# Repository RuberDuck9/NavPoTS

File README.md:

# NavPoTS
The integrated navigation, power, and telemtry system.

(placeholder name btw)

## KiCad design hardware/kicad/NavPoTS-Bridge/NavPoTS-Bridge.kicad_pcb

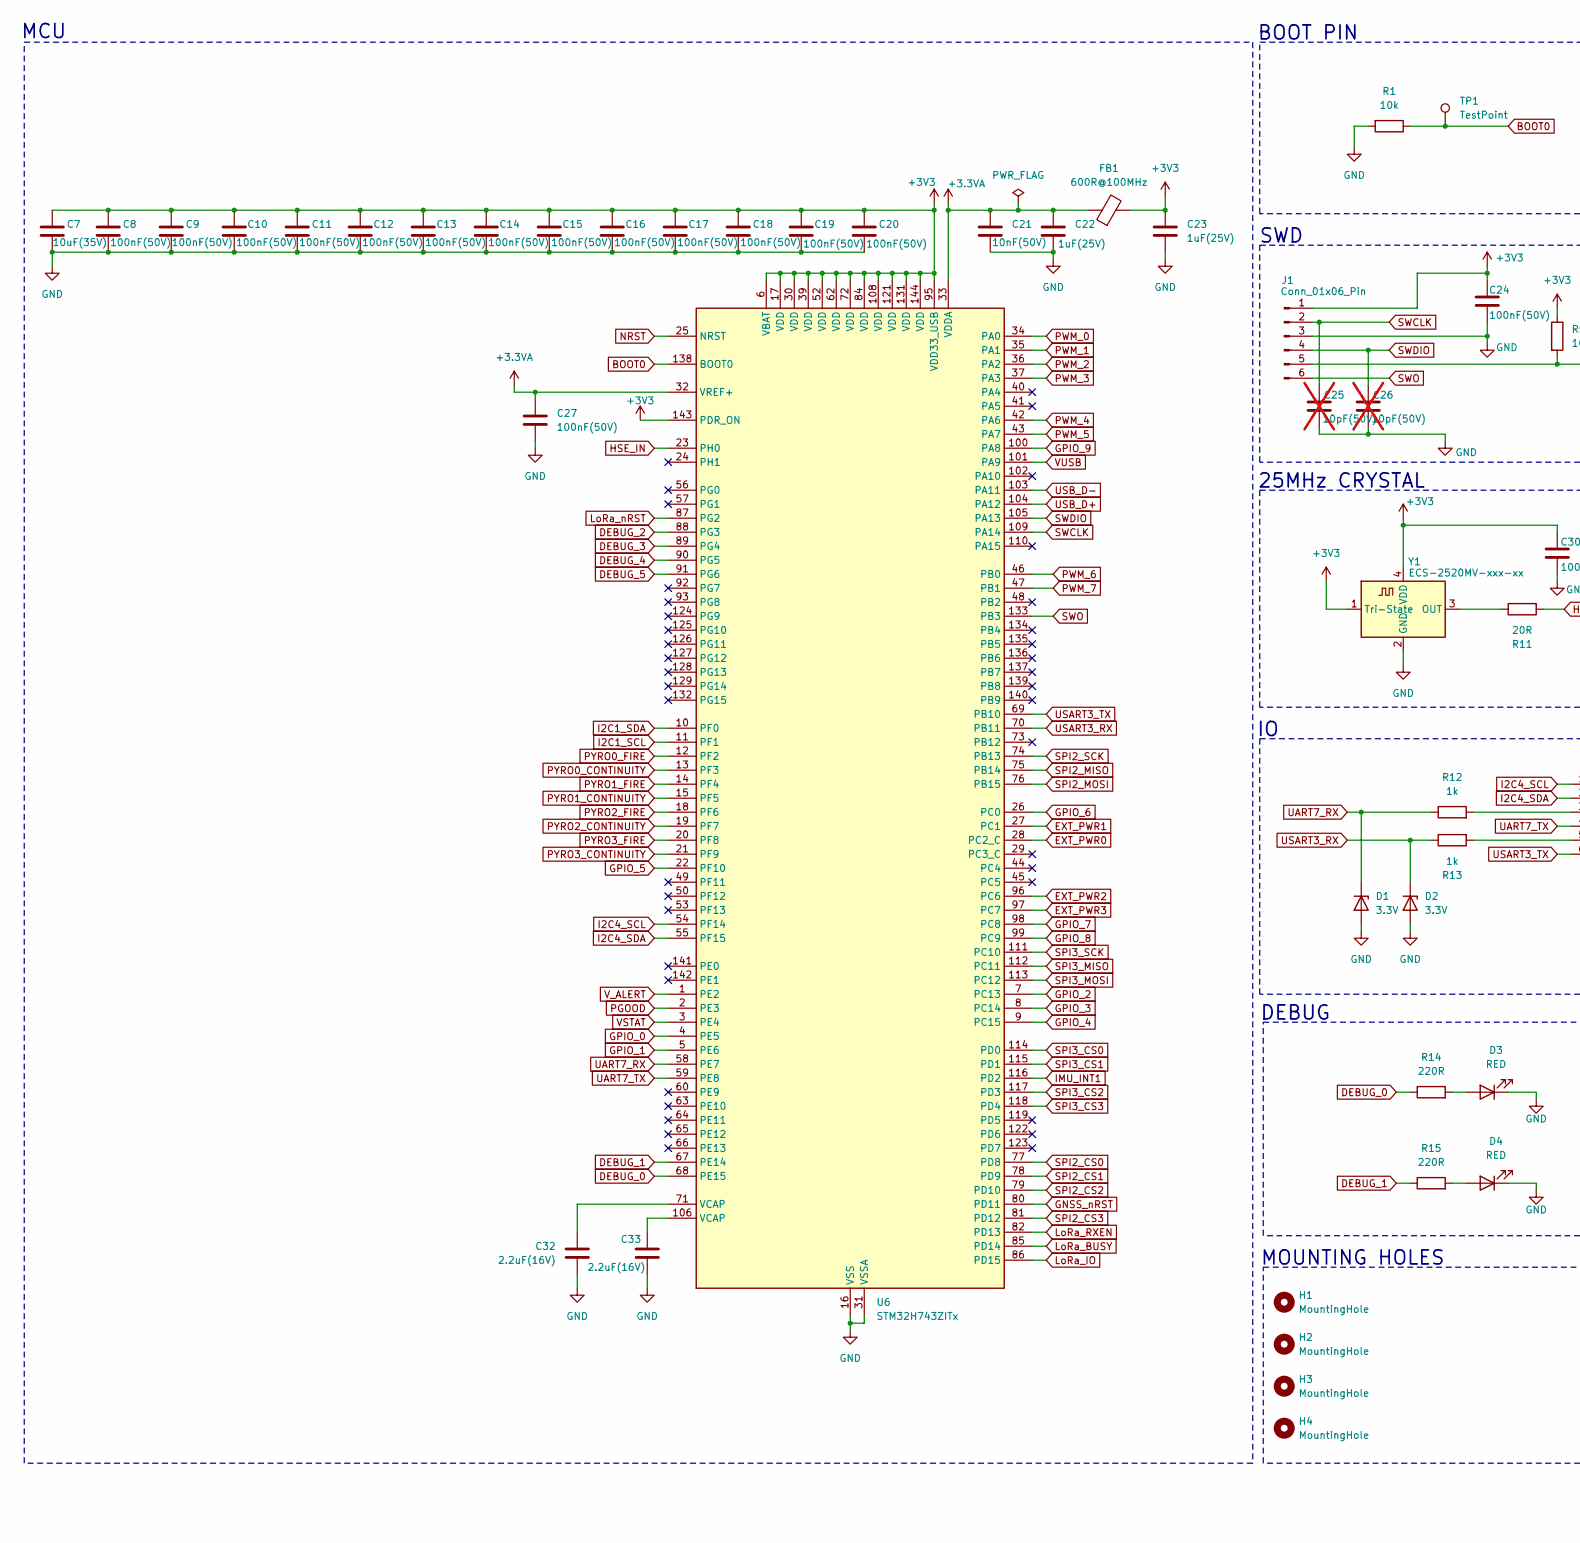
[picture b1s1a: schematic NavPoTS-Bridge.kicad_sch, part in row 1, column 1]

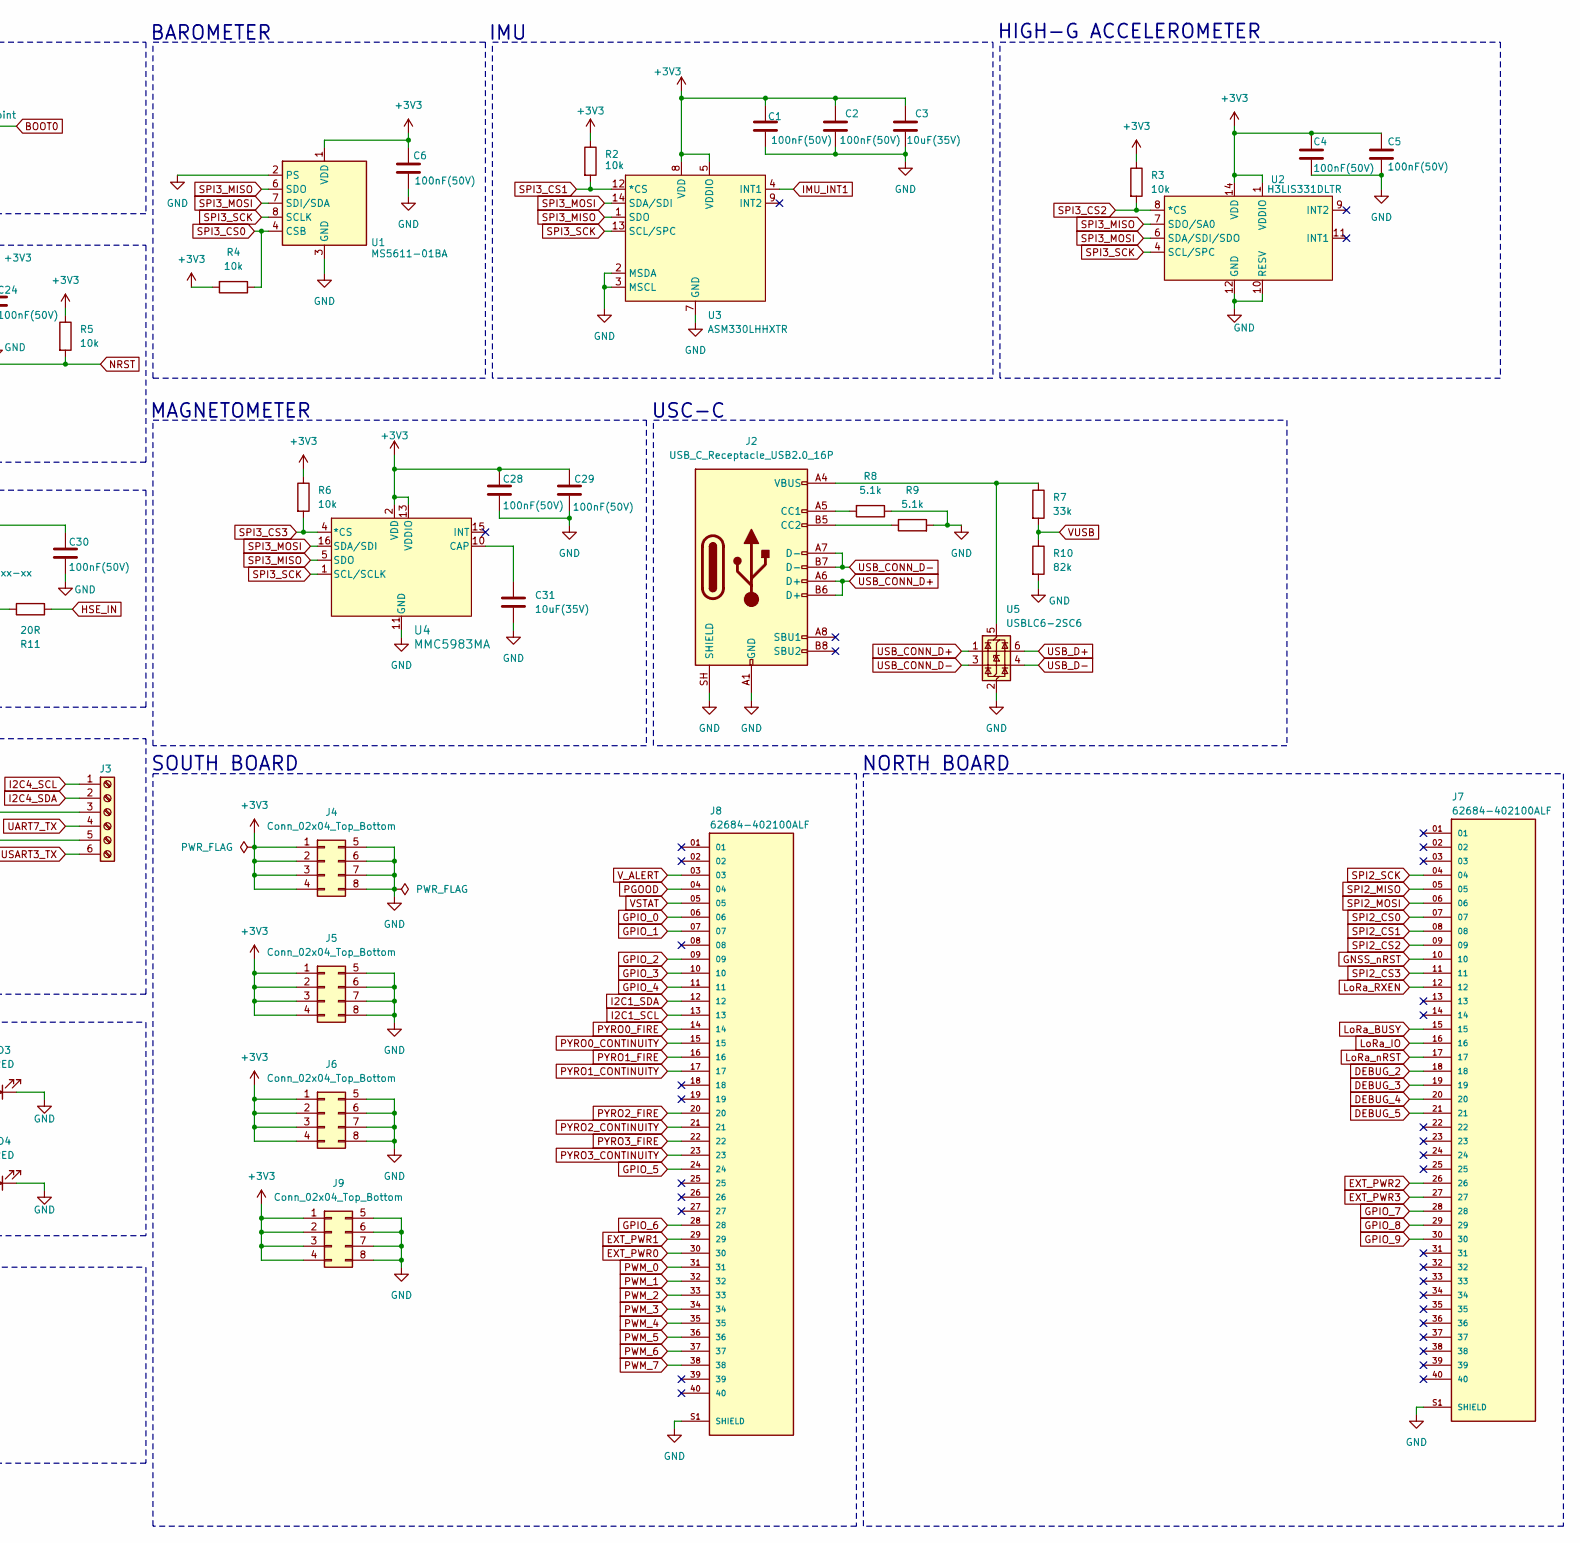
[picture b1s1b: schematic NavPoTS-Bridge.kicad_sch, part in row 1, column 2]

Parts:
C1, C2, C4, C5, C6, C8, C9, C10, C11, C12, C13, C14, C15, C16, C17, C18, C19, C20, C24, C27, C28, C29, C30: 100nF(50V); C_0603_1608Metric_Pad1.08x0.95mm_HandSolder; MPN C0603C104K5RACTU
C3, C7, C31: 10uF(35V); C_0603_1608Metric_Pad1.08x0.95mm_HandSolder; MPN GRM188R6YA106MA73D
C21: 10nF(50V); C_0603_1608Metric_Pad1.08x0.95mm_HandSolder; MPN C0603C103K5RACTU
C22, C23: 1uF(25V); C_0603_1608Metric_Pad1.08x0.95mm_HandSolder; MPN CL10B105KA8NNNC
C25, C26: 10pF(50V); C_0603_1608Metric_Pad1.08x0.95mm_HandSolder; MPN C0603C100J5GACTU; not fitted
C32, C33: 2.2uF(16V); C_0603_1608Metric_Pad1.08x0.95mm_HandSolder; MPN CL10A225KO8NNNC
D1, D2: 3.3V; D_SOD-123; MPN MMSZ3V3T1G
D3, D4: RED; LED_0603_1608Metric_Pad1.05x0.95mm_HandSolder; MPN LTST-C190KRKT
FB1: 600R@100MHz; L_0805_2012Metric_Pad1.05x1.20mm_HandSolder; MPN HZ0805E601R-10
H1, H2, H3, H4: MountingHole; MountingHole_3.2mm_M3
J1: Conn_01x06_Pin; PinHeader_1x06_P2.54mm_Vertical
J2: USB_C_Receptacle_USB2.0_16P; USB_C_Receptacle_GCT_USB4105-xx-A_16P_TopMnt_Horizontal; MPN USB4105-GF-A
J3: Screw_Terminal_01x06; CONN_ED555_6DS; MPN ED555/6DS
J4, J5, J6, J9: Conn_02x04_Top_Bottom; PinHeader_2x04_P2.54mm_Vertical; MPN PEC14SAGN
J7, J8: 62684-402100ALF; Amphenol_62684-402100ALF; MPN 62684-402100ALF
R1, R2, R3, R4, R5, R6: 10k; R_0603_1608Metric_Pad0.98x0.95mm_HandSolder; MPN RC0603FR-0710KL
R7: 33k; R_0603_1608Metric_Pad0.98x0.95mm_HandSolder; MPN RC0603FR-0733KL
R8, R9: 5.1k; R_0603_1608Metric_Pad0.98x0.95mm_HandSolder; MPN RC0603FR-075K1L
R10: 82k; R_0603_1608Metric_Pad0.98x0.95mm_HandSolder; MPN RC0603FR-0782KL
R11: 20R; R_0603_1608Metric_Pad0.98x0.95mm_HandSolder; MPN RC0603FR-0720RL
R12, R13: 1k; R_0603_1608Metric_Pad0.98x0.95mm_HandSolder; MPN RC0603FR-071KL
R14, R15: 220R; R_0603_1608Metric_Pad0.98x0.95mm_HandSolder; MPN RC0603FR-07220RL
TP1: TestPoint; TestPoint_Pad_D1.5mm
U1: MS5611-01BA; LGA-8_3x5mm_P1.25mm; MPN MS561101BA03-50
U2: H3LIS331DLTR; TFLGA16_3X3X1_STM-M; MPN H3LIS331DLTR
U3: ASM330LHHXTR; LGA-14_3x2.5mm_P0.5mm_LayoutBorder3x4y; MPN ASM330LHHXTR
U4: MMC5983MA; LGA-16_3x3mm_P0.5mm; MPN MMC5983MA
U5: USBLC6-2SC6; SOT-23-6; MPN USBLC6-2SC6
U6: STM32H743ZITx; LQFP-144_20x20mm_P0.5mm; MPN STM32H743ZIT6
Y1: ECS-2520MV-xxx-xx; Oscillator_SMD_ECS_2520MV-xxx-xx-4Pin_2.5x2.0mm; MPN ECS-2520MV-250-CN-TR

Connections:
+3.3VA: C21.1, C22.1, C27.2, FB1.1, U6.32 (VREF+), U6.33 (VDDA)
+3V3: C1.1, C2.1, C3.1, C4.1, C5.1, C6.1, C7.1, C8.1, C9.1, C10.1, C11.1, C12.1, C13.1, C14.1, C15.1, C16.1, C17.1, C18.1, C19.1, C20.1, C23.1, C24.1, C28.1, C29.1, C30.1, FB1.2, J1.1, J4.1, J4.2, J4.3, J4.4, J5.1, J5.2, J5.3, J5.4, J6.1, J6.2, J6.3, J6.4, J9.1, J9.2, J9.3, J9.4, R2.1, R3.1, R4.2, R5.1, R6.1, U1.1 (VDD), U2.1 (VDDIO), U2.14 (VDD), U2.15 (RESV), U3.5 (VDDIO), U3.8 (VDD), U4.2 (VDD), U4.13 (VDDIO), U6.6 (VBAT), U6.17 (VDD), U6.30 (VDD), U6.39 (VDD), U6.52 (VDD), U6.62 (VDD), U6.72 (VDD), U6.84 (VDD), U6.95 (VDD33_USB), U6.108 (VDD), U6.121 (VDD), U6.131 (VDD), U6.143 (PDR_ON), U6.144 (VDD), Y1.1 (Tri-State), Y1.4 (VDD)
BOOT0: R1.1, TP1.1 (1_1), U6.138 (BOOT0)
DEBUG_0: R14.1, U6.68 (PE15)
DEBUG_1: R15.1, U6.67 (PE14)
DEBUG_2: J7.18, U6.88 (PG3)
DEBUG_3: J7.19, U6.89 (PG4)
DEBUG_4: J7.20, U6.90 (PG5)
DEBUG_5: J7.21, U6.91 (PG6)
EXT_PWR0: J8.30, U6.28 (PC2_C)
EXT_PWR1: J8.29, U6.27 (PC1)
EXT_PWR2: J7.26, U6.96 (PC6)
EXT_PWR3: J7.27, U6.97 (PC7)
GND: C1.2, C2.2, C3.2, C4.2, C5.2, C6.2, C7.2, C8.2, C9.2, C10.2, C11.2, C12.2, C13.2, C14.2, C15.2, C16.2, C17.2, C18.2, C19.2, C20.2, C21.2, C22.2, C23.2, C24.2, C25.2, C26.2, C27.1, C28.2, C29.2, C30.2, C31.2, C32.1, C33.1, D1.2 (A), D2.2 (A), D3.1 (K), D4.1 (K), J1.3, J2.A1 (GND), J2.A12 (GND), J2.B1 (GND), J2.B12 (GND), J2.SH (SHIELD), J4.5, J4.6, J4.7, J4.8, J5.5, J5.6, J5.7, J5.8, J6.5, J6.6, J6.7, J6.8, J7.S1 (SHIELD), J7.S2 (SHIELD), J8.S1 (SHIELD), J8.S2 (SHIELD), J9.5, J9.6, J9.7, J9.8, R1.2, R8.1, R9.2, R10.2, U1.2 (PS), U1.3 (GND), U2.5 (GND), U2.10 (RESV), U2.12 (GND), U2.13 (GND), U2.16 (GND), U3.2 (MSDA), U3.3 (MSCL), U3.7 (GND), U4.9 (GND), U4.11 (GND), U5.2 (GND), U6.16 (VSS), U6.31 (VSSA), U6.38 (VSS), U6.51 (VSS), U6.61 (VSS), U6.83 (VSS), U6.94 (VSS), U6.107 (VSS), U6.120 (VSS), U6.130 (VSS), Y1.2 (GND)
GNSS_nRST: J7.10, U6.80 (PD11)
GPIO_0: J8.06, U6.4 (PE5)
GPIO_1: J8.07, U6.5 (PE6)
GPIO_2: J8.09, U6.7 (PC13)
GPIO_3: J8.10, U6.8 (PC14)
GPIO_4: J8.11, U6.9 (PC15)
GPIO_5: J8.24, U6.22 (PF10)
GPIO_6: J8.28, U6.26 (PC0)
GPIO_7: J7.28, U6.98 (PC8)
GPIO_8: J7.29, U6.99 (PC9)
GPIO_9: J7.30, U6.100 (PA8)
HSE_IN: R11.2, U6.23 (PH0)
I2C1_SCL: J8.13, U6.11 (PF1)
I2C1_SDA: J8.12, U6.10 (PF0)
I2C4_SCL: J3.1, U6.54 (PF14)
I2C4_SDA: J3.2, U6.55 (PF15)
IMU_INT1: U3.4 (INT1), U6.116 (PD2)
LoRa_BUSY: J7.15, U6.85 (PD14)
LoRa_IO: J7.16, U6.86 (PD15)
LoRa_RXEN: J7.12, U6.82 (PD13)
LoRa_nRST: J7.17, U6.87 (PG2)
NRST: J1.5, R5.2, U6.25 (NRST)
unnamed: C32.2, U6.71 (VCAP)
unnamed: C33.2, U6.106 (VCAP)
unnamed: D3.2 (A), R14.2
unnamed: D4.2 (A), R15.2
unnamed: J2.A5 (CC1), R8.2
unnamed: J2.B5 (CC2), R9.1
unnamed: J3.3, R12.2
unnamed: J3.5, R13.2
unnamed: C31.1, U4.10 (CAP)
unnamed: J2.A4 (VBUS), J2.A9 (VBUS), J2.B4 (VBUS), J2.B9 (VBUS), R7.1, U5.5 (VBUS)
unnamed: R11.1, Y1.3 (OUT)
PGOOD: J8.04, U6.2 (PE3)
PWM_0: J8.31, U6.34 (PA0)
PWM_1: J8.32, U6.35 (PA1)
PWM_2: J8.33, U6.36 (PA2)
PWM_3: J8.34, U6.37 (PA3)
PWM_4: J8.35, U6.42 (PA6)
PWM_5: J8.36, U6.43 (PA7)
PWM_6: J8.37, U6.46 (PB0)
PWM_7: J8.38, U6.47 (PB1)
PYRO0_CONTINUITY: J8.15, U6.13 (PF3)
PYRO0_FIRE: J8.14, U6.12 (PF2)
PYRO1_CONTINUITY: J8.17, U6.15 (PF5)
PYRO1_FIRE: J8.16, U6.14 (PF4)
PYRO2_CONTINUITY: J8.21, U6.19 (PF7)
PYRO2_FIRE: J8.20, U6.18 (PF6)
PYRO3_CONTINUITY: J8.23, U6.21 (PF9)
PYRO3_FIRE: J8.22, U6.20 (PF8)
SPI2_CS0: J7.07, U6.77 (PD8)
SPI2_CS1: J7.08, U6.78 (PD9)
SPI2_CS2: J7.09, U6.79 (PD10)
SPI2_CS3: J7.11, U6.81 (PD12)
SPI2_MISO: J7.05, U6.75 (PB14)
SPI2_MOSI: J7.06, U6.76 (PB15)
SPI2_SCK: J7.04, U6.74 (PB13)
SPI3_CS0: R4.1, U1.4 (CSB), U1.5 (CSB), U6.114 (PD0)
SPI3_CS1: R2.2, U3.12 (*CS), U6.115 (PD1)
SPI3_CS2: R3.2, U2.8 (*CS), U6.117 (PD3)
SPI3_CS3: R6.2, U4.4 (*CS), U6.118 (PD4)
SPI3_MISO: U1.6 (SDO), U2.7 (SDO/SA0), U3.1 (SDO), U4.5 (SDO), U6.112 (PC11)
SPI3_MOSI: U1.7 (SDI/SDA), U2.6 (SDA/SDI/SDO), U3.14 (SDA/SDI), U4.16 (SDA/SDI), U6.113 (PC12)
SPI3_SCK: U1.8 (SCLK), U2.4 (SCL/SPC), U3.13 (SCL/SPC), U4.1 (SCL/SCLK), U6.111 (PC10)
SWCLK: C25.1, J1.2, U6.109 (PA14)
SWDIO: C26.1, J1.4, U6.105 (PA13)
SWO: J1.6, U6.133 (PB3)
UART7_RX: D1.1 (K), R12.1, U6.58 (PE7)
UART7_TX: J3.4, U6.59 (PE8)
USART3_RX: D2.1 (K), R13.1, U6.70 (PB11)
USART3_TX: J3.6, U6.69 (PB10)
USB_CONN_D+: J2.A6 (D+), J2.B6 (D+), U5.1 (I/O1)
USB_CONN_D-: J2.A7 (D-), J2.B7 (D-), U5.3 (I/O2)
USB_D+: U5.6 (I/O1), U6.104 (PA12)
USB_D-: U5.4 (I/O2), U6.103 (PA11)
VSTAT: J8.05, U6.3 (PE4)
VUSB: R7.2, R10.1, U6.101 (PA9)
V_ALERT: J8.03, U6.1 (PE2)

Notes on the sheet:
BAROMETER
MAGNETOMETER
USC-C
NORTH BOARD
MCU
HIGH-G ACCELEROMETER
IMU
25MHz CRYSTAL
BOOT PIN
SWD
MOUNTING HOLES
DEBUG
SOUTH BOARD

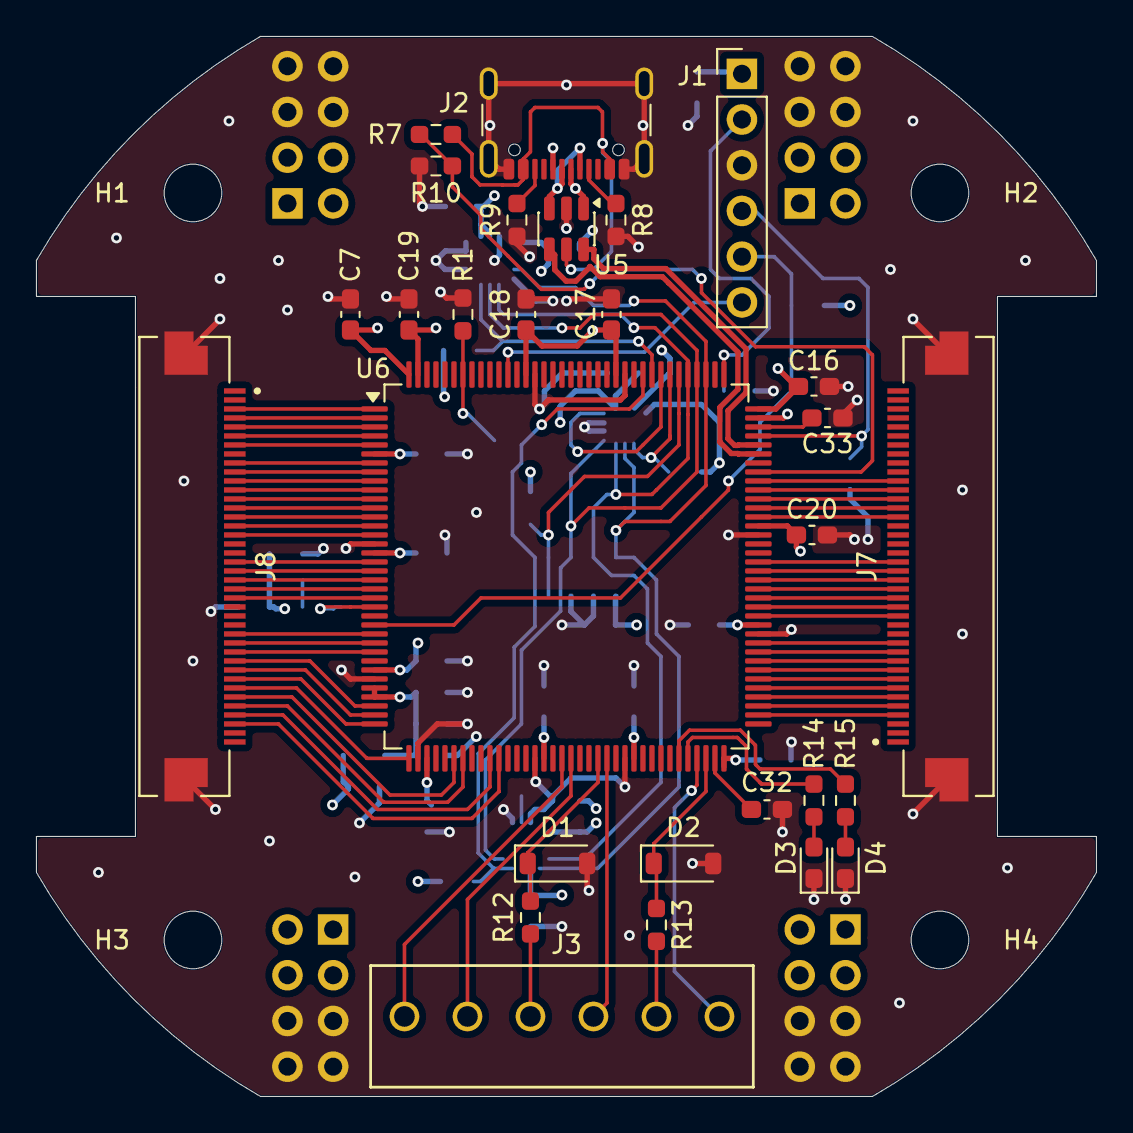
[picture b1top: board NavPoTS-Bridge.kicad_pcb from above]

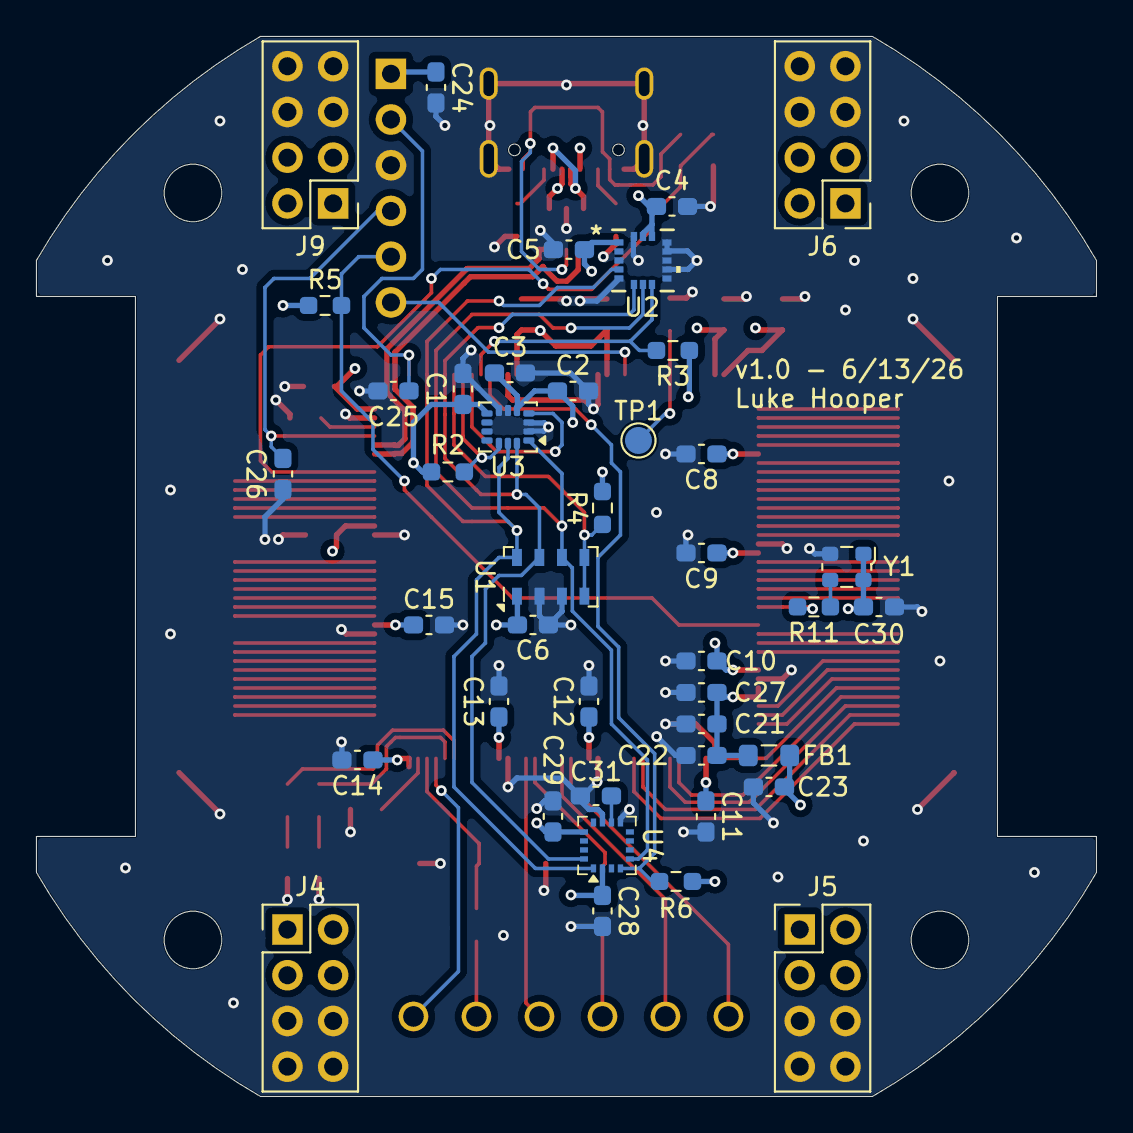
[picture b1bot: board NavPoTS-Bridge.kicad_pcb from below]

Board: 4 copper layers, 58.9 x 58.9 mm, 74 parts (42 on the bottom side), 92 nets.

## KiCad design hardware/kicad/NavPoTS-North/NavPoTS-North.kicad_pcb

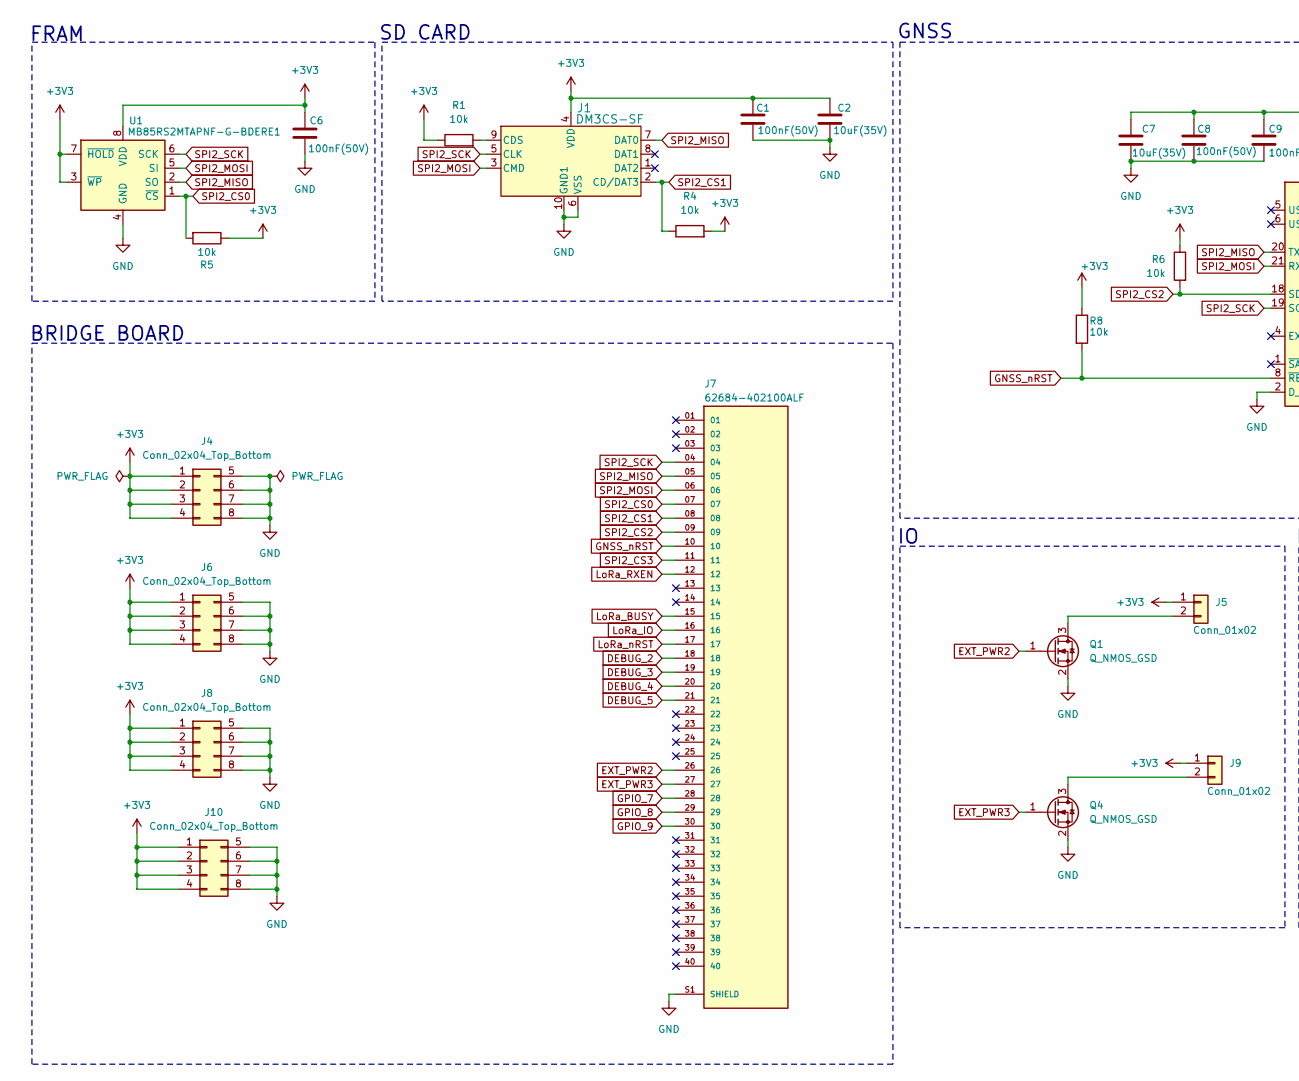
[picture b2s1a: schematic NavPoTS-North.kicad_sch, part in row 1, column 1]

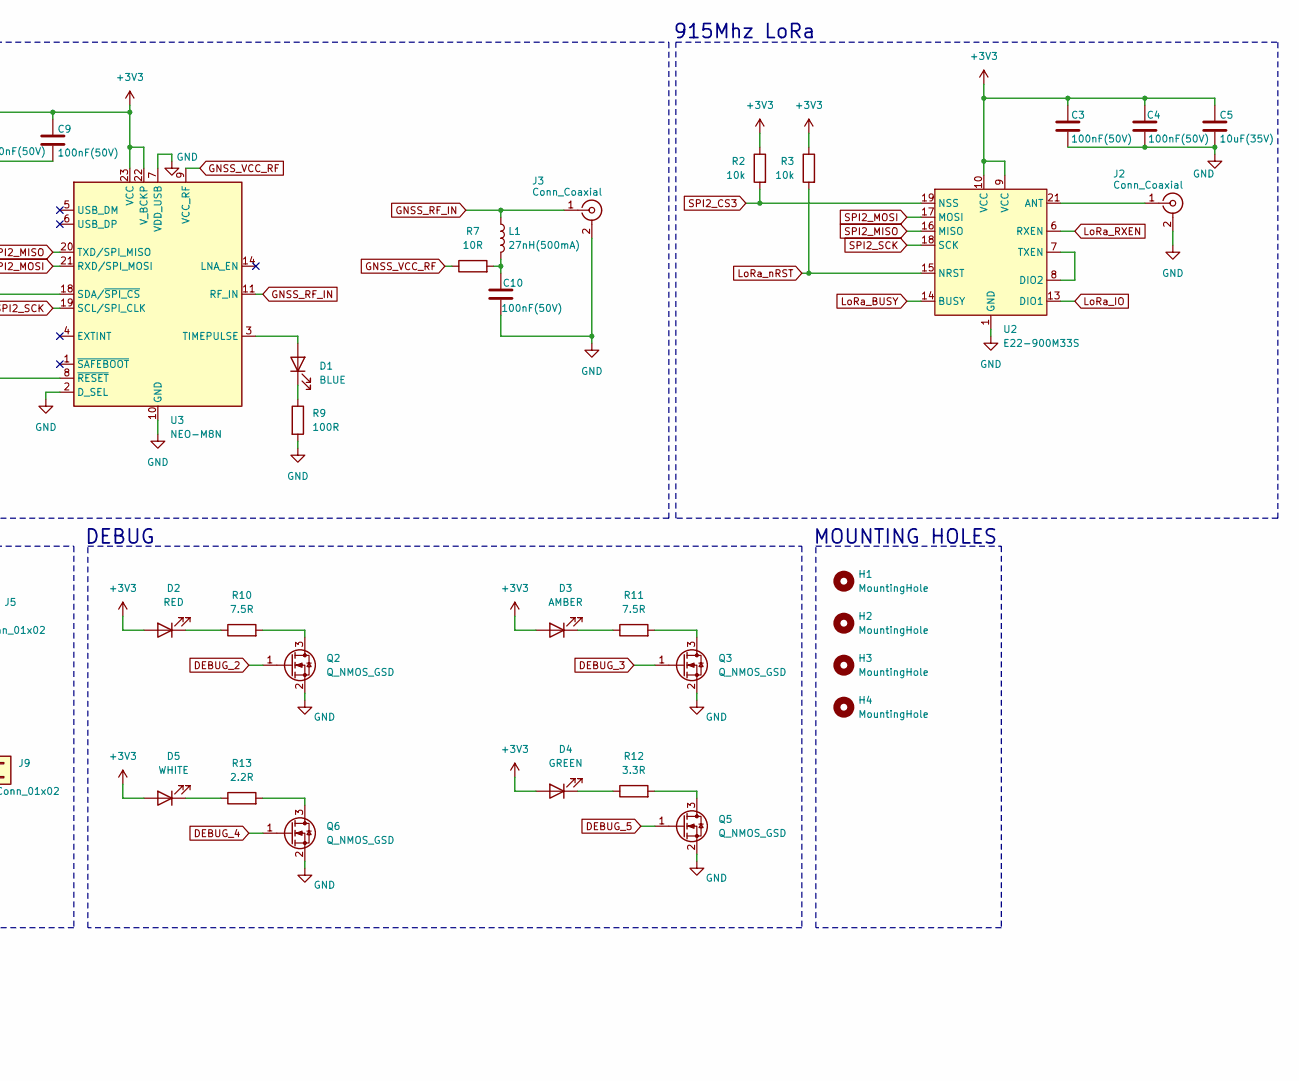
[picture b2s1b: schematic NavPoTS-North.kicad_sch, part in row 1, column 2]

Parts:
C1, C3, C4, C6, C8, C9, C10: 100nF(50V); C_0603_1608Metric_Pad1.08x0.95mm_HandSolder; MPN C0603C104K5RACTU
C2, C5, C7: 10uF(35V); C_0603_1608Metric_Pad1.08x0.95mm_HandSolder; MPN GRM188R6YA106MA73D
D1: BLUE; LED_0603_1608Metric_Pad1.05x0.95mm_HandSolder; MPN LTST-C193TBKT-5A
D2: RED; LED_PLCC_2835_Handsoldering; MPN JE2835ARD-N-0001A0000-N0000001
D3: AMBER; LED_PLCC_2835_Handsoldering; MPN JE2835AAM-N-0001A0000-N0000001
D4: GREEN; LED_PLCC_2835_Handsoldering; MPN JE2835AGR-N-0002A0000-N0000001
D5: WHITE; LED_PLCC_2835_Handsoldering; MPN JE2835AWT-R-H40GA0000-N0000001
H1, H2, H3, H4: MountingHole; MountingHole_3.2mm_M3
J1: DM3CS-SF; DM3CS-SF_HIR; MPN DM3CS-SF
J2, J3: Conn_Coaxial; COAX4GND_CONSMA001-C-G_TEC; MPN CONSMA001-C-G
J4, J6, J8, J10: Conn_02x04_Top_Bottom; PinSocket_2x04_P2.54mm_Vertical; MPN 61300821821
J5, J9: Conn_01x02; JST_XH_B2B-XH-A_1x02_P2.50mm_Vertical; MPN B2B-XH-A
J7: 62684-402100ALF; Amphenol_62684-402100ALF; MPN 62684-402100ALF
L1: 27nH(500mA); L_0603_1608Metric_Pad1.05x0.95mm_HandSolder; MPN LQG18HN27NJ00D
Q1, Q4: Q_NMOS_GSD; SOT-23-3; MPN AO3400A
Q2, Q3, Q5, Q6: Q_NMOS_GSD; SOT-523; MPN DMG1012TQ-7
R1, R2, R3, R4, R5, R6, R8: 10k; R_0603_1608Metric_Pad0.98x0.95mm_HandSolder; MPN RC0603FR-0710KL
R7: 10R; R_0603_1608Metric_Pad0.98x0.95mm_HandSolder; MPN RC0603FR-0710RL
R9: 100R; R_0603_1608Metric_Pad0.98x0.95mm_HandSolder; MPN RC0603FR-07100RL
R10, R11: 7.5R; R_0603_1608Metric_Pad0.98x0.95mm_HandSolder; MPN RC0603FR-077R5L
R12: 3.3R; R_0603_1608Metric_Pad0.98x0.95mm_HandSolder; MPN RC0603FR-073R3L
R13: 2.2R; R_0603_1608Metric_Pad0.98x0.95mm_HandSolder; MPN RC0603FR-072R2L
U1: MB85RS2MTAPNF-G-BDERE1; SOIC-8_3.9x4.9mm_P1.27mm; MPN MB85RS2MTAPNF-G-BDERE1
U2: E22-900M33S; MPN E22-900M33S
U3: NEO-M8N; MPN NEO-M8N-0

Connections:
+3V3: C1.1, C2.1, C3.1, C4.1, C5.1, C6.1, C7.1, C8.1, C9.1, D2.2 (A), D3.2 (A), D4.2 (A), D5.2 (A), J1.4 (VDD), J4.1, J4.2, J4.3, J4.4, J5.1, J6.1, J6.2, J6.3, J6.4, J8.1, J8.2, J8.3, J8.4, J9.1, J10.1, J10.2, J10.3, J10.4, R1.1, R2.1, R3.1, R4.2, R5.1, R6.1, R8.1, U1.3 (~WP), U1.7 (~HOLD), U1.8 (VDD), U2.9 (VCC), U2.10 (VCC), U3.22 (V_BCKP), U3.23 (VCC)
DEBUG_2: J7.18, Q2.1 (G)
DEBUG_3: J7.19, Q3.1 (G)
DEBUG_4: J7.20, Q6.1 (G)
DEBUG_5: J7.21, Q5.1 (G)
EXT_PWR2: J7.26, Q1.1 (G)
EXT_PWR3: J7.27, Q4.1 (G)
GND: C1.2, C2.2, C3.2, C4.2, C5.2, C6.2, C7.2, C8.2, C9.2, C10.2, J1.6 (VSS), J1.10 (GND1), J1.11 (GND2), J1.12 (GND3), J1.13 (GND4), J2.2 (Ext), J3.2 (Ext), J4.5, J4.6, J4.7, J4.8, J6.5, J6.6, J6.7, J6.8, J7.S1 (SHIELD), J7.S2 (SHIELD), J8.5, J8.6, J8.7, J8.8, J10.5, J10.6, J10.7, J10.8, Q1.2 (S), Q2.2 (S), Q3.2 (S), Q4.2 (S), Q5.2 (S), Q6.2 (S), R9.2, U1.4 (GND), U2.1 (GND), U2.2 (GND), U2.3 (GND), U2.4 (GND), U2.5 (GND), U2.11 (GND), U2.12 (GND), U2.20 (GND), U2.22 (GND), U3.2 (D_SEL), U3.7 (VDD_USB), U3.10 (GND), U3.12 (GND), U3.13 (GND), U3.24 (GND)
GNSS_RF_IN: J3.1 (In), L1.1, U3.11 (RF_IN)
GNSS_VCC_RF: R7.1, U3.9 (VCC_RF)
GNSS_nRST: J7.10, R8.2, U3.8 (~RESET)
GPIO_7: J7.28
GPIO_8: J7.29
GPIO_9: J7.30
LoRa_BUSY: J7.15, U2.14 (BUSY)
LoRa_IO: J7.16, U2.13 (DIO1)
LoRa_RXEN: J7.12, U2.6 (RXEN)
LoRa_nRST: J7.17, R3.2, U2.15 (NRST)
unnamed: C10.1, L1.2, R7.2
unnamed: D1.2 (A), U3.3 (TIMEPULSE)
unnamed: D1.1 (K), R9.1
unnamed: D2.1 (K), R10.1
unnamed: D3.1 (K), R11.1
unnamed: D4.1 (K), R12.1
unnamed: D5.1 (K), R13.1
unnamed: J1.9 (CDS), R1.2
unnamed: J2.1 (In), U2.21 (ANT)
unnamed: J5.2, Q1.3 (D)
unnamed: J9.2, Q4.3 (D)
unnamed: Q2.3 (D), R10.2
unnamed: Q3.3 (D), R11.2
unnamed: Q5.3 (D), R12.2
unnamed: Q6.3 (D), R13.2
unnamed: U2.7 (TXEN), U2.8 (DIO2)
SPI2_CS0: J7.07, R5.2, U1.1 (~CS)
SPI2_CS1: J1.2 (CD/DAT3), J7.08, R4.1
SPI2_CS2: J7.09, R6.2, U3.18 (SDA/~SPI_CS)
SPI2_CS3: J7.11, R2.2, U2.19 (NSS)
SPI2_MISO: J1.7 (DAT0), J7.05, U1.2 (SO), U2.16 (MISO), U3.20 (TXD/SPI_MISO)
SPI2_MOSI: J1.3 (CMD), J7.06, U1.5 (SI), U2.17 (MOSI), U3.21 (RXD/SPI_MOSI)
SPI2_SCK: J1.5 (CLK), J7.04, U1.6 (SCK), U2.18 (SCK), U3.19 (SCL/SPI_CLK)

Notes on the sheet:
GNSS
SD CARD
DEBUG
915Mhz LoRa
BRIDGE BOARD
MOUNTING HOLES
FRAM

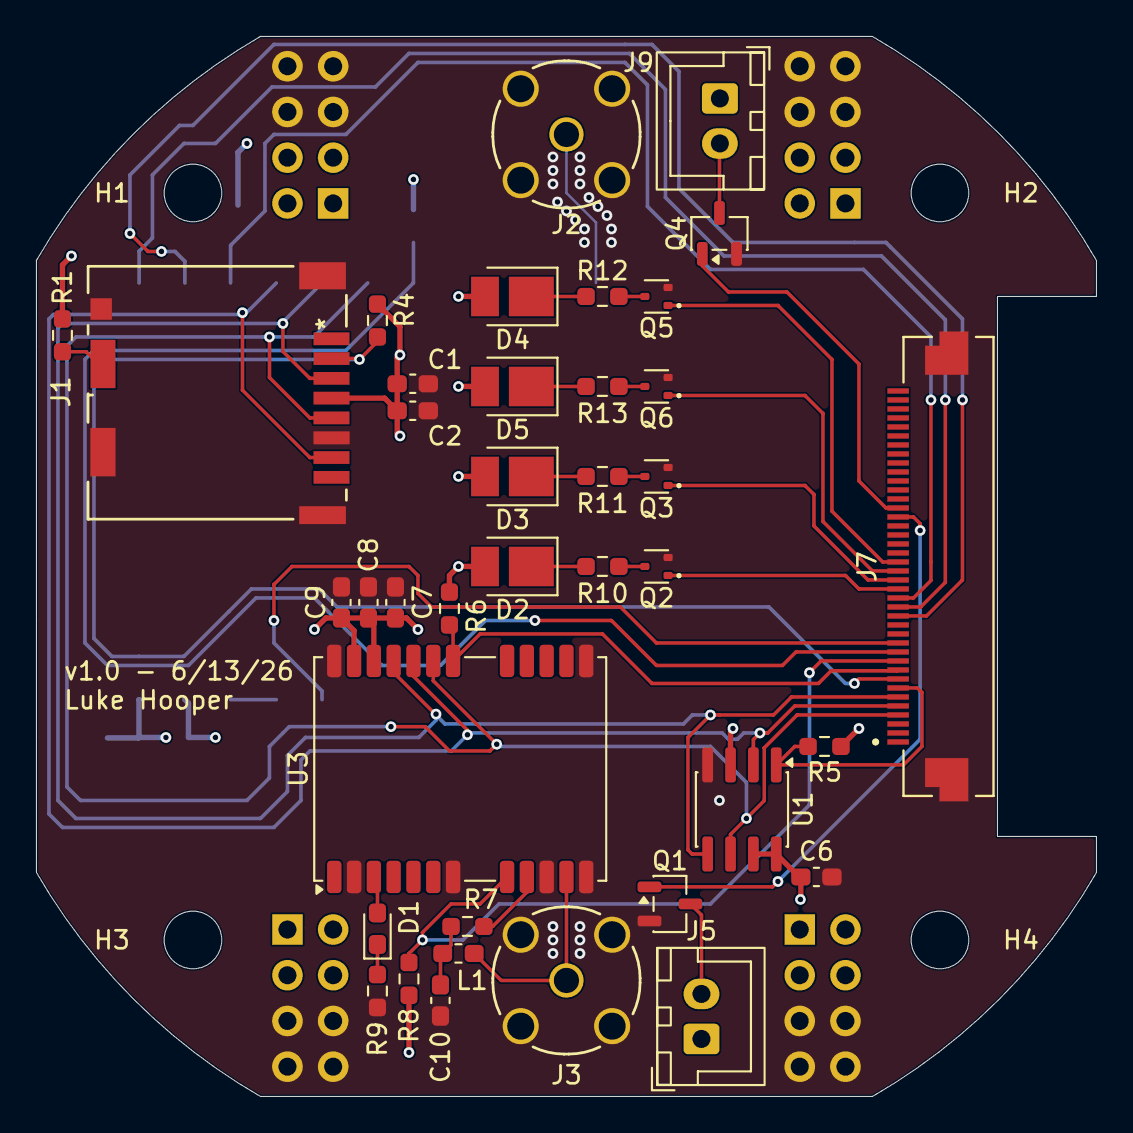
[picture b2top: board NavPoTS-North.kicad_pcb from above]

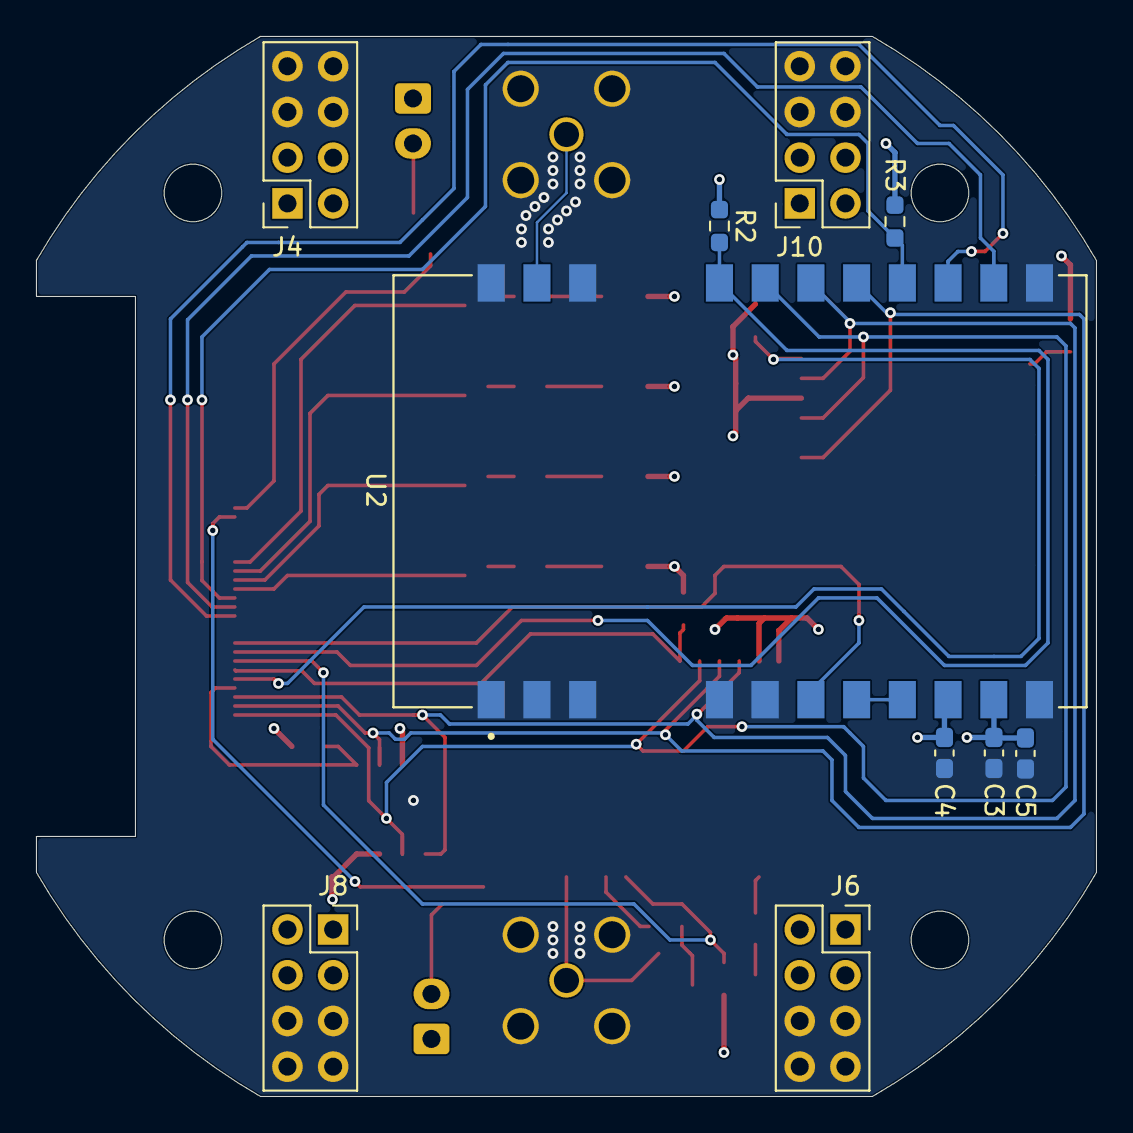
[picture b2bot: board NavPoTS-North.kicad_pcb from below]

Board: 4 copper layers, 58.9 x 58.9 mm, 52 parts (10 on the bottom side), 38 nets.
